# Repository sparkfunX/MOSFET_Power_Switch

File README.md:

SparkFun MOSFET Power Switch
========================================

[*SparkFun MOSFET Power Switch (COM-19799)*](https://www.sparkfun.com/products/19799)

Does your Arduino need to control a high voltage item, like a 12V LED strip, while needing to be powered as well? Do you want to avoid having multiple power adapters for your project and your Arduino? The MOSFET Power Switch is one of those products that we needed ourselves at SparkFun, so we figured other folks may have the same problem. Power the board with up to 12V and control up to 10A, all while providing sweet sweet 3.3V to your control board.

This board is ideal for turning on and off large loads such as solenoids, LEDs strips, and DC loads that may have back EMF. Simply pull the CTL pin low to activate the load. 3.3V, GND, and VCC are also provided at PTH headers. The load can be inserted into the poke-home connectors or soldered into PTH holes.

The MOSFET ([PSMN7R0-100BS](https://cdn.sparkfun.com/assets/6/9/3/8/1/PSMN7R0-100BS.pdf)) is rated to 100A/100V but we don't recommend you go much above 10A as the PCB traces become the limiter. The board 

Repository Contents
-------------------

* **/Hardware** - Eagle design files (.brd, .sch)

License Information
-------------------

This product is _**open source**_! 

Please review the LICENSE.md file for license information. 

If you have any questions or concerns on licensing, please contact technical support on our [SparkFun forums](https://forum.sparkfun.com/viewforum.php?f=152).

Distributed as-is; no warranty is given.

- Your friends at SparkFun.

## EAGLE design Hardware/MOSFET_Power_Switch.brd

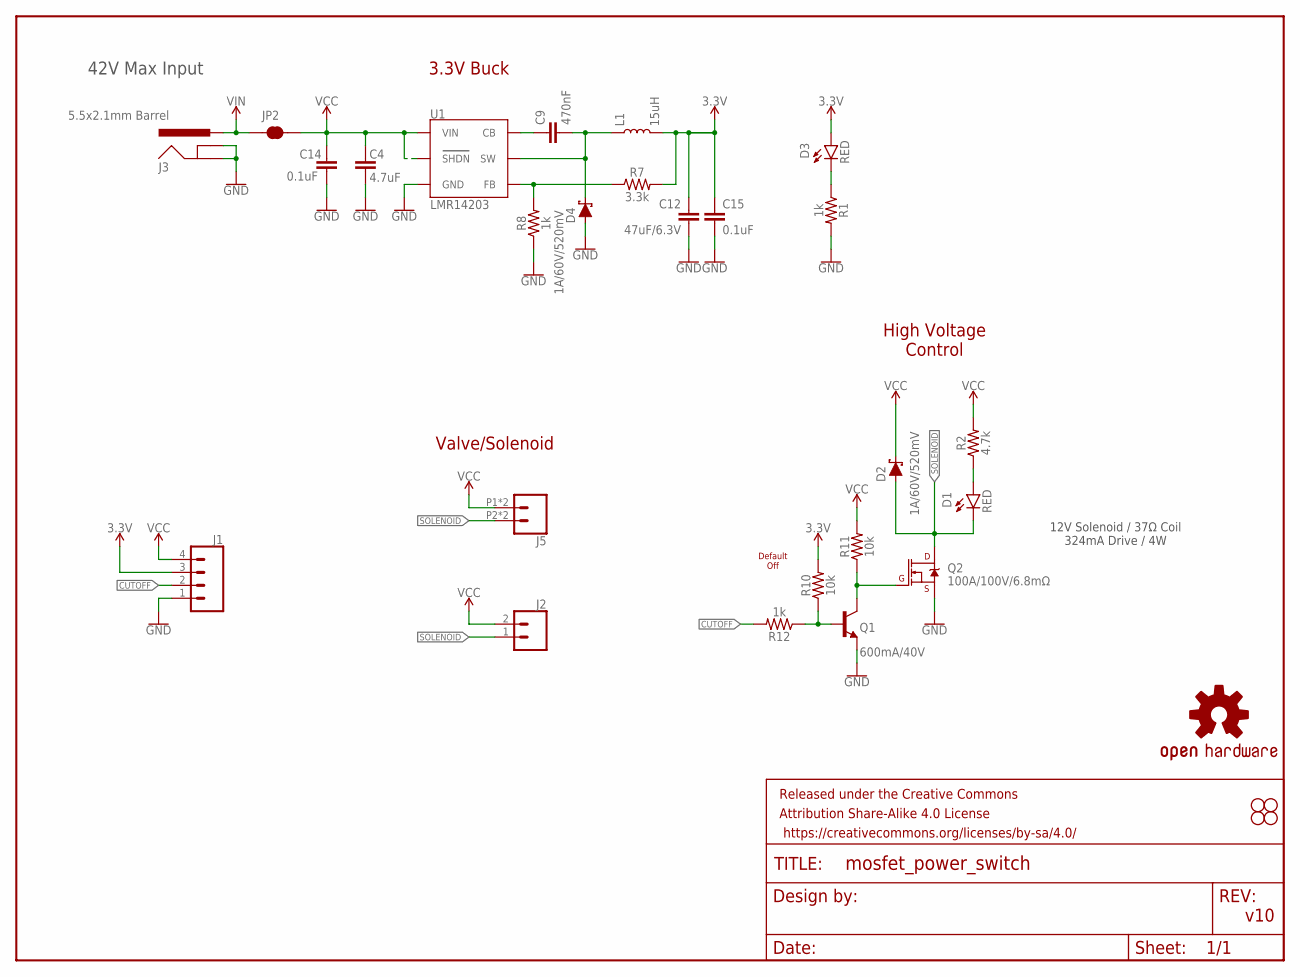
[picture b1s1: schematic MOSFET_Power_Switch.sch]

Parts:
C4: 4.7uF; 0603
C9: 470nF; 0603
C12: 47uF/6.3V; 0805
C14, C15: 0.1uF; 0603
D1, D3: RED; LED-0603
D2, D4: 1A/60V/520mV; DIODE-MICRO-SMP
FRAME2: FRAME-LETTER; CREATIVE_COMMONS
H1, H2, H3, H4: STAND-OFF
J1: CONN_041X04_NO_SILK_NO_POP; 1X04_NO_SILK
J2: CONN_021X02_NO_SILK; 1X02_NO_SILK
J3: 5.5x2.1mm Barrel; POWER_JACK_SMD
J5: CONN_02SMALL_POKEHOME; 1X02_POKEHOME
JP2: JUMPER-COMBO_2_NC_TRACE; COMBO-JUMPER_2_NC_TRACE
L1: 15uH; INDUCTOR_LQH32
LOGO1: OSHW-LOGOS; OSHW-LOGO-S
Q1: 600mA/40V; SOT23-3
Q2: 100A/100V/6.8mΩ; TO-263/D2PAK
R1, R8, R12: 1k; 0603
R2: 4.7k; 0603
R7: 3.3k; 0603
R10, R11: 10k; 0603
U1: LMR14203; SOT23-6

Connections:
3.3V: C12.1, C15.1, D3.A, J1.3, L1.P$2 (2), R7.2, R10.2
CUTOFF: J1.2, R12.2
GND: C4.2, C12.2, C14.2, C15.2, D4.A, J1.1, J3.GND (GNDBREAK), J3.P$4 (GND), Q1.2 (E), Q2.3 (S), R1.2, R8.1, U1.2 (GND)
unnamed: Q1.3 (C), Q2.1 (G), R11.1
unnamed: D1.A, R2.1
unnamed: D3.C, R1.1
unnamed: R7.1, R8.2, U1.3 (FB)
unnamed: C9.1, U1.1 (CB)
unnamed: Q1.1 (B), R10.1, R12.1
SOLENOID: D1.C, D2.A, J2.1, J5.P2 (2), J5.P4 (2), Q2.2 (D)
VCC: C4.1, C14.1, D2.C, J1.4, J2.2, J5.P1 (1), J5.P3 (1), JP2.2, JP2.4 (2), R2.2, R11.2, U1.4 (SHDN), U1.5 (VIN)
VIN: J3.VIN0 (PWR), JP2.1, JP2.3 (1)
VSW: C9.2, D4.C, L1.P$1 (1), U1.6 (SW)

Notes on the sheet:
v10
Default Off
Valve/Solenoid
High Voltage Control
3.3V Buck
12V Solenoid / 37Ω Coil 324mA Drive / 4W
42V Max Input

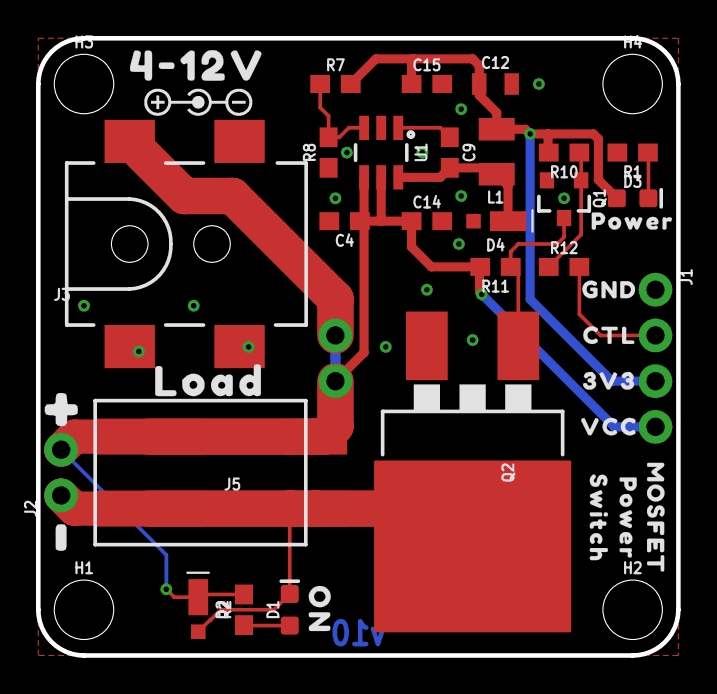
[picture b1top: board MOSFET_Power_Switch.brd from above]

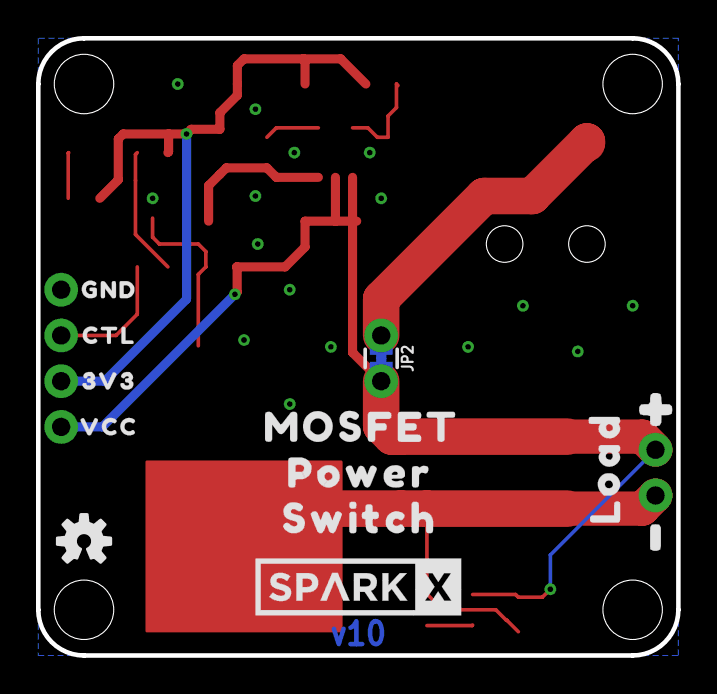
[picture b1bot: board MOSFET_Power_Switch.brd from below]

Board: 2 copper layers, 35.6 x 34.3 mm, 56 parts (13 on the bottom side), 13 nets.

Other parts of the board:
U$1, U$17: 3V32
U$2: MOSFET0
U$3, U$15: GND0
U$5, U$19: LOAD0
U$6: 4#12V0
U$7, U$18: VCC3
U$8, U$16: CTL0
U$9: POWER1
U$10, U$20: #0
U$11, U$22: #1
U$13: SWITCH2
U$21: SPARKX-LOGO5; SPARKX-LARGE
U$23: POWER0
U$24: MOSFET_0
U$25: POWER_1
U$26: SWITCH_2
U$29: POLARITY_MARKING_CENTER_POSITIVE#JPG
U$49: ON0

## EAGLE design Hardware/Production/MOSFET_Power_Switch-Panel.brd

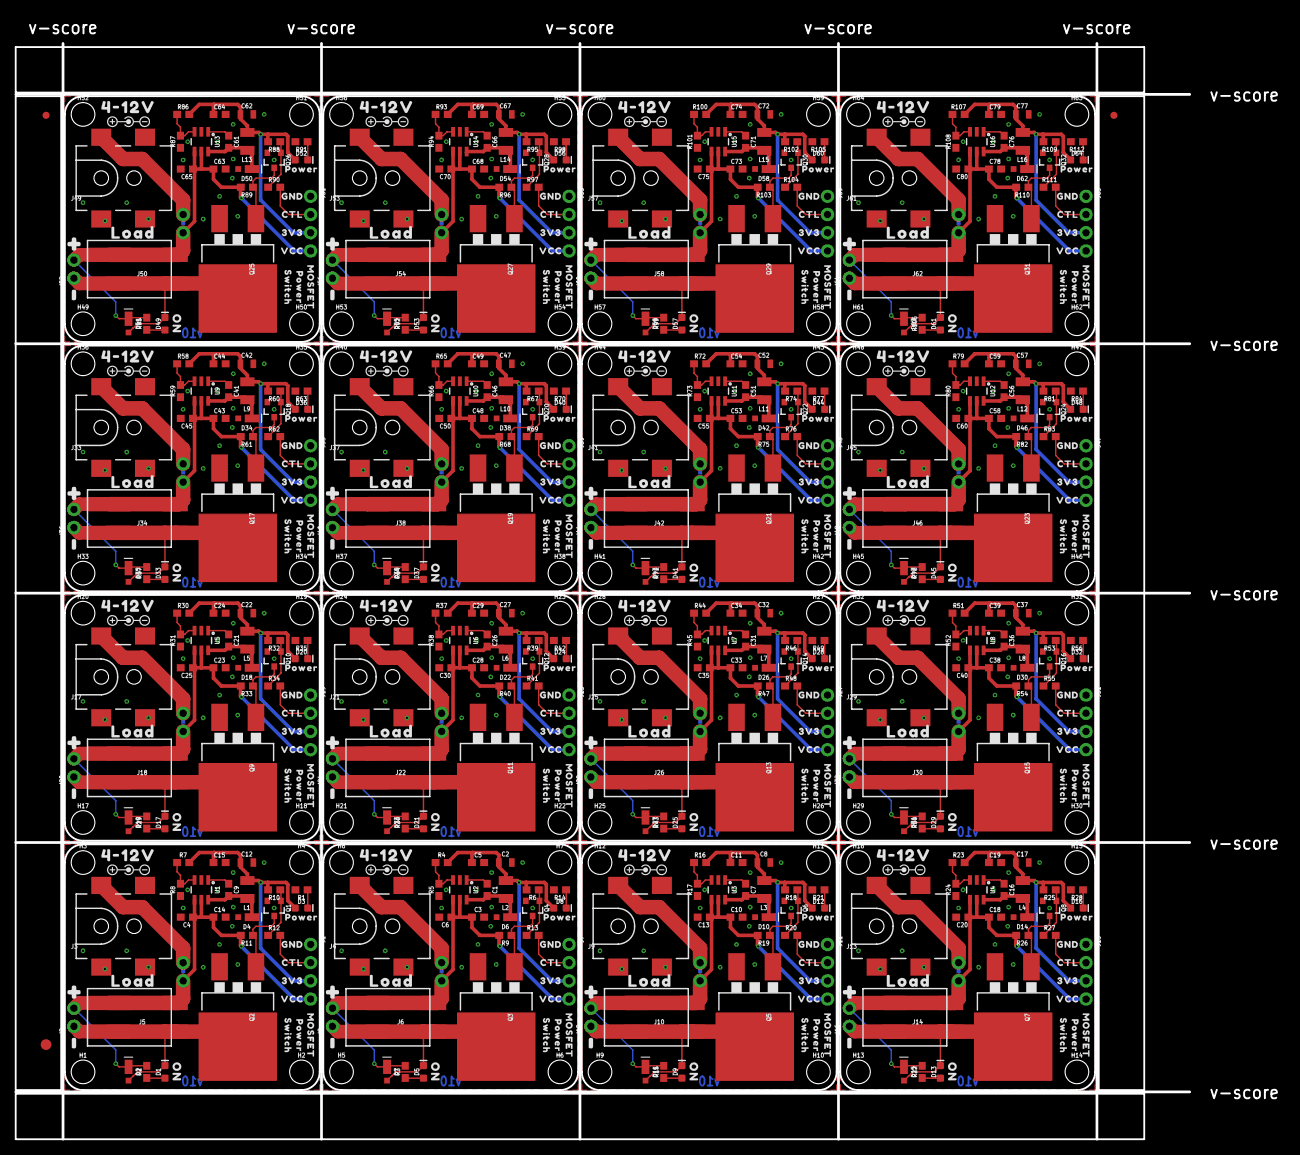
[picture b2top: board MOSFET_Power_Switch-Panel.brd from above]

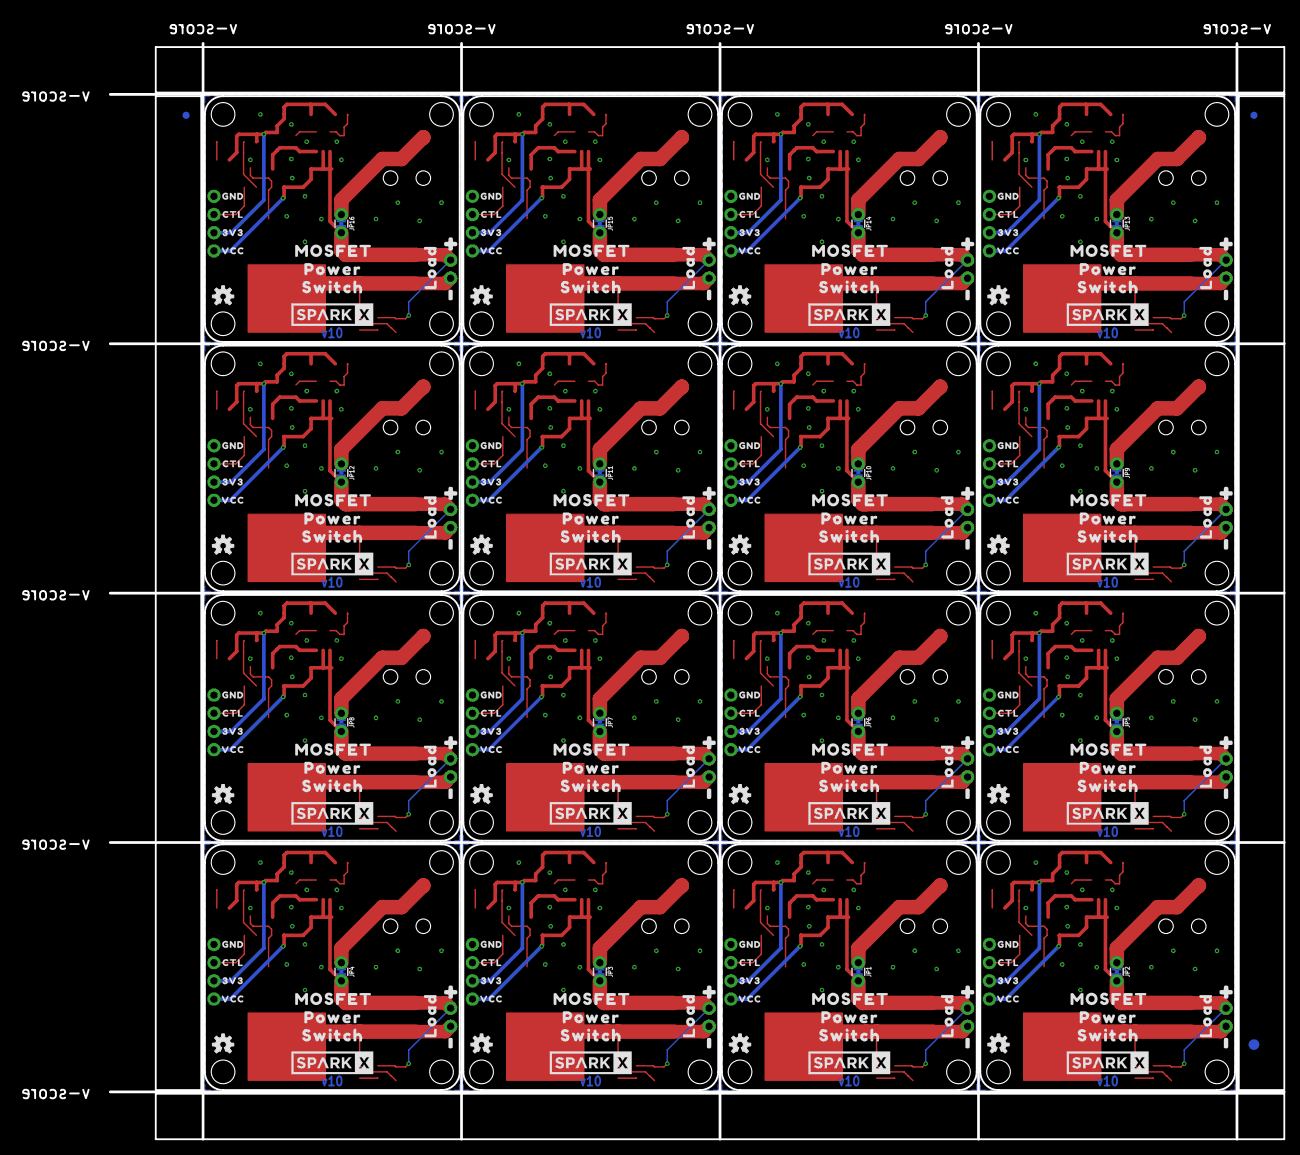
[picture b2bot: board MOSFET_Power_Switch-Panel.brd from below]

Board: 2 copper layers, 177.0 x 156.8 mm, 886 parts (211 on the bottom side), 208 nets.

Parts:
C1, C7, C9, C16, C21, C26, C31, C36, C41, C46, C51, C56, C61, C66, C71, C76: 470nF; 0603
C2, C8, C12, C17, C22, C27, C32, C37, C42, C47, C52, C57, C62, C67, C72, C77: 47uF/6.3V; 0805
C3, C5, C10, C11, C14, C15, C18, C19, C23, C24, C28, C29, C33, C34, C38, C39, C43, C44, C48, C49, C53, C54, C58, C59, C63, C64, C68, C69, C73, C74, C78, C79: 0.1uF; 0603
C4, C6, C13, C20, C25, C30, C35, C40, C45, C50, C55, C60, C65, C70, C75, C80: 4.7uF; 0603
D1, D3, D5, D8, D9, D12, D13, D16, D17, D20, D21, D24, D25, D28, D29, D32, D33, D36, D37, D40, D41, D44, D45, D48, D49, D52, D53, D56, D57, D60, D61, D64: RED; LED-0603
D2, D4, D6, D7, D10, D11, D14, D15, D18, D19, D22, D23, D26, D27, D30, D31, D34, D35, D38, D39, D42, D43, D46, D47, D50, D51, D54, D55, D58, D59, D62, D63: 1A/60V/520mV; DIODE-MICRO-SMP
E$1, E$2, E$3, E$4: FIDUCIAL-1X2
E$5, E$6: FIDUCIAL-1.5X3
H1, H2, H3, H4, H5, H6, H7, H8, H9, H10, H11, H12, H13, H14, H15, H16, H17, H18, H19, H20, H21, H22, H23, H24, H25, H26, H27, H28, H29, H30, H31, H32, H33, H34, H35, H36, H37, H38, H39, H40, H41, H42, H43, H44, H45, H46, H47, H48, H49, H50, H51, H52, H53, H54, H55, H56, H57, H58, H59, H60, H61, H62, H63, H64: STAND-OFF
J1, J7, J11, J15, J19, J23, J27, J31, J35, J39, J43, J47, J51, J55, J59, J63: 1X04_NO_SILK
J2, J8, J12, J16, J20, J24, J28, J32, J36, J40, J44, J48, J52, J56, J60, J64: 1X02_NO_SILK
J3, J4, J9, J13, J17, J21, J25, J29, J33, J37, J41, J45, J49, J53, J57, J61: 5.5x2.1mm Barrel; POWER_JACK_SMD
J5, J6, J10, J14, J18, J22, J26, J30, J34, J38, J42, J46, J50, J54, J58, J62: 1X02_POKEHOME
JP1, JP2, JP3, JP4, JP5, JP6, JP7, JP8, JP9, JP10, JP11, JP12, JP13, JP14, JP15, JP16: JUMPER-COMBO_2_NC_TRACE; COMBO-JUMPER_2_NC_TRACE
L1, L2, L3, L4, L5, L6, L7, L8, L9, L10, L11, L12, L13, L14, L15, L16: 15uH; INDUCTOR_LQH32
LOGO1, LOGO2, LOGO3, LOGO4, LOGO5, LOGO6, LOGO7, LOGO8, LOGO9, LOGO10, LOGO11, LOGO12, LOGO13, LOGO14, LOGO15, LOGO16: OSHW-LOGOS; OSHW-LOGO-S
Q1, Q4, Q6, Q8, Q10, Q12, Q14, Q16, Q18, Q20, Q22, Q24, Q26, Q28, Q30, Q32: 600mA/40V; SOT23-3
Q2, Q3, Q5, Q7, Q9, Q11, Q13, Q15, Q17, Q19, Q21, Q23, Q25, Q27, Q29, Q31: 100A/100V/6.8mΩ; TO-263/D2PAK
R1, R5, R8, R12, R13, R14, R17, R20, R21, R24, R27, R28, R31, R34, R35, R38, R41, R42, R45, R48, R49, R52, R55, R56, R59, R62, R63, R66, R69, R70, R73, R76, R77, R80, R83, R84, R87, R90, R91, R94, R97, R98, R101, R104, R105, R108, R111, R112: 1k; 0603
R2, R3, R15, R22, R29, R36, R43, R50, R57, R64, R71, R78, R85, R92, R99, R106: 4.7k; 0603
R4, R7, R16, R23, R30, R37, R44, R51, R58, R65, R72, R79, R86, R93, R100, R107: 3.3k; 0603
R6, R9, R10, R11, R18, R19, R25, R26, R32, R33, R39, R40, R46, R47, R53, R54, R60, R61, R67, R68, R74, R75, R81, R82, R88, R89, R95, R96, R102, R103, R109, R110: 10k; 0603
U1, U2, U3, U4, U5, U6, U7, U8, U9, U10, U11, U12, U13, U14, U15, U16: LMR14203; SOT23-6
U$1, U$17, U$31, U$38, U$57, U$64, U$82, U$89, U$107, U$114, U$132, U$139, U$157, U$164, U$182, U$189, U$207, U$214, U$232, U$239, U$257, U$264, U$282, U$289, U$307, U$314, U$332, U$339, U$357, U$364, U$382, U$389: 3V32
U$2, U$43, U$69, U$94, U$119, U$144, U$169, U$194, U$219, U$244, U$269, U$294, U$319, U$344, U$369, U$394: MOSFET0
U$3, U$15, U$32, U$36, U$58, U$62, U$83, U$87, U$108, U$112, U$133, U$137, U$158, U$162, U$183, U$187, U$208, U$212, U$233, U$237, U$258, U$262, U$283, U$287, U$308, U$312, U$333, U$337, U$358, U$362, U$383, U$387: GND0
U$4, U$21, U$51, U$76, U$101, U$126, U$151, U$176, U$201, U$226, U$251, U$276, U$301, U$326, U$351, U$376: SPARKX-LOGO5; SPARKX-LARGE
U$5, U$19, U$30, U$40, U$56, U$66, U$81, U$91, U$106, U$116, U$131, U$141, U$156, U$166, U$181, U$191, U$206, U$216, U$231, U$241, U$256, U$266, U$281, U$291, U$306, U$316, U$331, U$341, U$356, U$366, U$381, U$391: LOAD0
U$6, U$35, U$61, U$86, U$111, U$136, U$161, U$186, U$211, U$236, U$261, U$286, U$311, U$336, U$361, U$386: 4#12V0
U$7, U$18, U$33, U$39, U$59, U$65, U$84, U$90, U$109, U$115, U$134, U$140, U$159, U$165, U$184, U$190, U$209, U$215, U$234, U$240, U$259, U$265, U$284, U$290, U$309, U$315, U$334, U$340, U$359, U$365, U$384, U$390: VCC3
U$8, U$16, U$34, U$37, U$60, U$63, U$85, U$88, U$110, U$113, U$135, U$138, U$160, U$163, U$185, U$188, U$210, U$213, U$235, U$238, U$260, U$263, U$285, U$288, U$310, U$313, U$335, U$338, U$360, U$363, U$385, U$388: CTL0
U$9, U$44, U$70, U$95, U$120, U$145, U$170, U$195, U$220, U$245, U$270, U$295, U$320, U$345, U$370, U$395: POWER1
U$10, U$20, U$27, U$41, U$54, U$67, U$79, U$92, U$104, U$117, U$129, U$142, U$154, U$167, U$179, U$192, U$204, U$217, U$229, U$242, U$254, U$267, U$279, U$292, U$304, U$317, U$329, U$342, U$354, U$367, U$379, U$392: #0
U$11, U$22, U$28, U$42, U$55, U$68, U$80, U$93, U$105, U$118, U$130, U$143, U$155, U$168, U$180, U$193, U$205, U$218, U$230, U$243, U$255, U$268, U$280, U$293, U$305, U$318, U$330, U$343, U$355, U$368, U$380, U$393: #1
U$12, U$49, U$52, U$77, U$102, U$127, U$152, U$177, U$202, U$227, U$252, U$277, U$302, U$327, U$352, U$377: ON0
U$13, U$45, U$71, U$96, U$121, U$146, U$171, U$196, U$221, U$246, U$271, U$296, U$321, U$346, U$371, U$396: SWITCH2
U$14, U$29, U$53, U$78, U$103, U$128, U$153, U$178, U$203, U$228, U$253, U$278, U$303, U$328, U$353, U$378: POLARITY_MARKING_CENTER_POSITIVE#JPG
U$23, U$46, U$72, U$97, U$122, U$147, U$172, U$197, U$222, U$247, U$272, U$297, U$322, U$347, U$372, U$397: POWER0
U$24, U$47, U$73, U$98, U$123, U$148, U$173, U$198, U$223, U$248, U$273, U$298, U$323, U$348, U$373, U$398: MOSFET_0
U$25, U$48, U$74, U$99, U$124, U$149, U$174, U$199, U$224, U$249, U$274, U$299, U$324, U$349, U$374, U$399: POWER_1
U$26, U$50, U$75, U$100, U$125, U$150, U$175, U$200, U$225, U$250, U$275, U$300, U$325, U$350, U$375, U$400: SWITCH_2

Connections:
3.3V: C12.1, C15.1, D3.A, J1.3, L1.P$2, R7.2, R10.2
3.3V1: C2.1, C5.1, D8.A, J7.3, L2.P$2, R4.2, R6.2
3.3V2: C8.1, C11.1, D12.A, J11.3, L3.P$2, R16.2, R18.2
3.3V3: C17.1, C19.1, D16.A, J15.3, L4.P$2, R23.2, R25.2
3.3V4: C22.1, C24.1, D20.A, J19.3, L5.P$2, R30.2, R32.2
3.3V5: C27.1, C29.1, D24.A, J23.3, L6.P$2, R37.2, R39.2
3.3V6: C32.1, C34.1, D28.A, J27.3, L7.P$2, R44.2, R46.2
3.3V7: C37.1, C39.1, D32.A, J31.3, L8.P$2, R51.2, R53.2
3.3V8: C42.1, C44.1, D36.A, J35.3, L9.P$2, R58.2, R60.2
3.3V9: C47.1, C49.1, D40.A, J39.3, L10.P$2, R65.2, R67.2
3.3V10: C52.1, C54.1, D44.A, J43.3, L11.P$2, R72.2, R74.2
3.3V11: C57.1, C59.1, D48.A, J47.3, L12.P$2, R79.2, R81.2
3.3V12: C62.1, C64.1, D52.A, J51.3, L13.P$2, R86.2, R88.2
3.3V13: C67.1, C69.1, D56.A, J55.3, L14.P$2, R93.2, R95.2
3.3V14: C72.1, C74.1, D60.A, J59.3, L15.P$2, R100.2, R102.2
3.3V15: C77.1, C79.1, D64.A, J63.3, L16.P$2, R107.2, R109.2
CUTOFF: J1.2, R12.2
CUTOFF1: J7.2, R13.2
CUTOFF2: J11.2, R20.2
CUTOFF3: J15.2, R27.2
CUTOFF4: J19.2, R34.2
CUTOFF5: J23.2, R41.2
CUTOFF6: J27.2, R48.2
CUTOFF7: J31.2, R55.2
CUTOFF8: J35.2, R62.2
CUTOFF9: J39.2, R69.2
CUTOFF10: J43.2, R76.2
CUTOFF11: J47.2, R83.2
CUTOFF12: J51.2, R90.2
CUTOFF13: J55.2, R97.2
CUTOFF14: J59.2, R104.2
CUTOFF15: J63.2, R111.2
GND: C4.2, C12.2, C14.2, C15.2, D4.A, J1.1, J3.GND, J3.P$4, Q1.2, Q2.3, R1.2, R8.1, U1.2
GND1: C2.2, C3.2, C5.2, C6.2, D6.A, J4.GND, J4.P$4, J7.1, Q3.3, Q4.2, R5.1, R14.2, U2.2
GND2: C8.2, C10.2, C11.2, C13.2, D10.A, J9.GND, J9.P$4, J11.1, Q5.3, Q6.2, R17.1, R21.2, U3.2
GND3: C17.2, C18.2, C19.2, C20.2, D14.A, J13.GND, J13.P$4, J15.1, Q7.3, Q8.2, R24.1, R28.2, U4.2
GND4: C22.2, C23.2, C24.2, C25.2, D18.A, J17.GND, J17.P$4, J19.1, Q9.3, Q10.2, R31.1, R35.2, U5.2
GND5: C27.2, C28.2, C29.2, C30.2, D22.A, J21.GND, J21.P$4, J23.1, Q11.3, Q12.2, R38.1, R42.2, U6.2
GND6: C32.2, C33.2, C34.2, C35.2, D26.A, J25.GND, J25.P$4, J27.1, Q13.3, Q14.2, R45.1, R49.2, U7.2
GND7: C37.2, C38.2, C39.2, C40.2, D30.A, J29.GND, J29.P$4, J31.1, Q15.3, Q16.2, R52.1, R56.2, U8.2
GND8: C42.2, C43.2, C44.2, C45.2, D34.A, J33.GND, J33.P$4, J35.1, Q17.3, Q18.2, R59.1, R63.2, U9.2
GND9: C47.2, C48.2, C49.2, C50.2, D38.A, J37.GND, J37.P$4, J39.1, Q19.3, Q20.2, R66.1, R70.2, U10.2
GND10: C52.2, C53.2, C54.2, C55.2, D42.A, J41.GND, J41.P$4, J43.1, Q21.3, Q22.2, R73.1, R77.2, U11.2
GND11: C57.2, C58.2, C59.2, C60.2, D46.A, J45.GND, J45.P$4, J47.1, Q23.3, Q24.2, R80.1, R84.2, U12.2
GND12: C62.2, C63.2, C64.2, C65.2, D50.A, J49.GND, J49.P$4, J51.1, Q25.3, Q26.2, R87.1, R91.2, U13.2
GND13: C67.2, C68.2, C69.2, C70.2, D54.A, J53.GND, J53.P$4, J55.1, Q27.3, Q28.2, R94.1, R98.2, U14.2
GND14: C72.2, C73.2, C74.2, C75.2, D58.A, J57.GND, J57.P$4, J59.1, Q29.3, Q30.2, R101.1, R105.2, U15.2
GND15: C77.2, C78.2, C79.2, C80.2, D62.A, J61.GND, J61.P$4, J63.1, Q31.3, Q32.2, R108.1, R112.2, U16.2
unnamed: Q1.3, Q2.1, R11.1
unnamed: D1.A, R2.1
unnamed: D3.C, R1.1
unnamed: D5.A, R3.1
unnamed: R7.1, R8.2, U1.3
unnamed: R4.1, R5.2, U2.3
unnamed: C1.1, U2.1
unnamed: Q3.1, Q4.3, R9.1
unnamed: Q4.1, R6.1, R13.1
unnamed: C9.1, U1.1
unnamed: D8.C, R14.1
unnamed: Q1.1, R10.1, R12.1
unnamed: D9.A, R15.1
unnamed: R16.1, R17.2, U3.3
unnamed: C7.1, U3.1
unnamed: Q5.1, Q6.3, R19.1
unnamed: Q6.1, R18.1, R20.1
unnamed: D12.C, R21.1
unnamed: D13.A, R22.1
unnamed: R23.1, R24.2, U4.3
unnamed: C16.1, U4.1
unnamed: Q7.1, Q8.3, R26.1
unnamed: Q8.1, R25.1, R27.1
unnamed: D16.C, R28.1
unnamed: D17.A, R29.1
unnamed: R30.1, R31.2, U5.3
unnamed: C21.1, U5.1
unnamed: Q9.1, Q10.3, R33.1
unnamed: Q10.1, R32.1, R34.1
unnamed: D20.C, R35.1
unnamed: D21.A, R36.1
unnamed: R37.1, R38.2, U6.3
unnamed: C26.1, U6.1
unnamed: Q11.1, Q12.3, R40.1
unnamed: Q12.1, R39.1, R41.1
unnamed: D24.C, R42.1
unnamed: D25.A, R43.1
unnamed: R44.1, R45.2, U7.3
unnamed: C31.1, U7.1
unnamed: Q13.1, Q14.3, R47.1
unnamed: Q14.1, R46.1, R48.1
unnamed: D28.C, R49.1
unnamed: D29.A, R50.1
unnamed: R51.1, R52.2, U8.3
unnamed: C36.1, U8.1
unnamed: Q15.1, Q16.3, R54.1
unnamed: Q16.1, R53.1, R55.1
unnamed: D32.C, R56.1
unnamed: D33.A, R57.1
unnamed: R58.1, R59.2, U9.3
unnamed: C41.1, U9.1
unnamed: Q17.1, Q18.3, R61.1
unnamed: Q18.1, R60.1, R62.1
unnamed: D36.C, R63.1
unnamed: D37.A, R64.1
unnamed: R65.1, R66.2, U10.3
unnamed: C46.1, U10.1
unnamed: Q19.1, Q20.3, R68.1
unnamed: Q20.1, R67.1, R69.1
unnamed: D40.C, R70.1
unnamed: D41.A, R71.1
unnamed: R72.1, R73.2, U11.3
unnamed: C51.1, U11.1
unnamed: Q21.1, Q22.3, R75.1
unnamed: Q22.1, R74.1, R76.1
unnamed: D44.C, R77.1
unnamed: D45.A, R78.1
unnamed: R79.1, R80.2, U12.3
unnamed: C56.1, U12.1
unnamed: Q23.1, Q24.3, R82.1
unnamed: Q24.1, R81.1, R83.1
unnamed: D48.C, R84.1
unnamed: D49.A, R85.1
unnamed: R86.1, R87.2, U13.3
unnamed: C61.1, U13.1
unnamed: Q25.1, Q26.3, R89.1
unnamed: Q26.1, R88.1, R90.1
unnamed: D52.C, R91.1
unnamed: D53.A, R92.1
unnamed: R93.1, R94.2, U14.3
unnamed: C66.1, U14.1
unnamed: Q27.1, Q28.3, R96.1
unnamed: Q28.1, R95.1, R97.1
unnamed: D56.C, R98.1
unnamed: D57.A, R99.1
unnamed: R100.1, R101.2, U15.3
unnamed: C71.1, U15.1
unnamed: Q29.1, Q30.3, R103.1
unnamed: Q30.1, R102.1, R104.1
unnamed: D60.C, R105.1
unnamed: D61.A, R106.1
unnamed: R107.1, R108.2, U16.3
unnamed: C76.1, U16.1
unnamed: Q31.1, Q32.3, R110.1
unnamed: Q32.1, R109.1, R111.1
unnamed: D64.C, R112.1
SOLENOID: D1.C, D2.A, J2.1, J5.P2, J5.P4, Q2.2
SOLENOID1: D5.C, D7.A, J6.P2, J6.P4, J8.1, Q3.2
SOLENOID2: D9.C, D11.A, J10.P2, J10.P4, J12.1, Q5.2
SOLENOID3: D13.C, D15.A, J14.P2, J14.P4, J16.1, Q7.2
SOLENOID4: D17.C, D19.A, J18.P2, J18.P4, J20.1, Q9.2
SOLENOID5: D21.C, D23.A, J22.P2, J22.P4, J24.1, Q11.2
SOLENOID6: D25.C, D27.A, J26.P2, J26.P4, J28.1, Q13.2
SOLENOID7: D29.C, D31.A, J30.P2, J30.P4, J32.1, Q15.2
SOLENOID8: D33.C, D35.A, J34.P2, J34.P4, J36.1, Q17.2
SOLENOID9: D37.C, D39.A, J38.P2, J38.P4, J40.1, Q19.2
SOLENOID10: D41.C, D43.A, J42.P2, J42.P4, J44.1, Q21.2
SOLENOID11: D45.C, D47.A, J46.P2, J46.P4, J48.1, Q23.2
SOLENOID12: D49.C, D51.A, J50.P2, J50.P4, J52.1, Q25.2
SOLENOID13: D53.C, D55.A, J54.P2, J54.P4, J56.1, Q27.2
SOLENOID14: D57.C, D59.A, J58.P2, J58.P4, J60.1, Q29.2
SOLENOID15: D61.C, D63.A, J62.P2, J62.P4, J64.1, Q31.2
VCC: C4.1, C14.1, D2.C, J1.4, J2.2, J5.P1, J5.P3, JP2.2, JP2.4, R2.2, R11.2, U1.4, U1.5
VCC1: C3.1, C6.1, D7.C, J6.P1, J6.P3, J7.4, J8.2, JP1.2, JP1.4, R3.2, R9.2, U2.4, U2.5
VCC2: C10.1, C13.1, D11.C, J10.P1, J10.P3, J11.4, J12.2, JP3.2, JP3.4, R15.2, R19.2, U3.4, U3.5
VCC3: C18.1, C20.1, D15.C, J14.P1, J14.P3, J15.4, J16.2, JP4.2, JP4.4, R22.2, R26.2, U4.4, U4.5
VCC4: C23.1, C25.1, D19.C, J18.P1, J18.P3, J19.4, J20.2, JP5.2, JP5.4, R29.2, R33.2, U5.4, U5.5
VCC5: C28.1, C30.1, D23.C, J22.P1, J22.P3, J23.4, J24.2, JP6.2, JP6.4, R36.2, R40.2, U6.4, U6.5
VCC6: C33.1, C35.1, D27.C, J26.P1, J26.P3, J27.4, J28.2, JP7.2, JP7.4, R43.2, R47.2, U7.4, U7.5
VCC7: C38.1, C40.1, D31.C, J30.P1, J30.P3, J31.4, J32.2, JP8.2, JP8.4, R50.2, R54.2, U8.4, U8.5
VCC8: C43.1, C45.1, D35.C, J34.P1, J34.P3, J35.4, J36.2, JP9.2, JP9.4, R57.2, R61.2, U9.4, U9.5
VCC9: C48.1, C50.1, D39.C, J38.P1, J38.P3, J39.4, J40.2, JP10.2, JP10.4, R64.2, R68.2, U10.4, U10.5
VCC10: C53.1, C55.1, D43.C, J42.P1, J42.P3, J43.4, J44.2, JP11.2, JP11.4, R71.2, R75.2, U11.4, U11.5
VCC11: C58.1, C60.1, D47.C, J46.P1, J46.P3, J47.4, J48.2, JP12.2, JP12.4, R78.2, R82.2, U12.4, U12.5
VCC12: C63.1, C65.1, D51.C, J50.P1, J50.P3, J51.4, J52.2, JP13.2, JP13.4, R85.2, R89.2, U13.4, U13.5
VCC13: C68.1, C70.1, D55.C, J54.P1, J54.P3, J55.4, J56.2, JP14.2, JP14.4, R92.2, R96.2, U14.4, U14.5
VCC14: C73.1, C75.1, D59.C, J58.P1, J58.P3, J59.4, J60.2, JP15.2, JP15.4, R99.2, R103.2, U15.4, U15.5
VCC15: C78.1, C80.1, D63.C, J62.P1, J62.P3, J63.4, J64.2, JP16.2, JP16.4, R106.2, R110.2, U16.4, U16.5
VIN: J3.VIN0, JP2.1, JP2.3
VIN1: J4.VIN0, JP1.1, JP1.3
VIN2: J9.VIN0, JP3.1, JP3.3
VIN3: J13.VIN0, JP4.1, JP4.3
VIN4: J17.VIN0, JP5.1, JP5.3
VIN5: J21.VIN0, JP6.1, JP6.3
VIN6: J25.VIN0, JP7.1, JP7.3
VIN7: J29.VIN0, JP8.1, JP8.3
VIN8: J33.VIN0, JP9.1, JP9.3
VIN9: J37.VIN0, JP10.1, JP10.3
VIN10: J41.VIN0, JP11.1, JP11.3
VIN11: J45.VIN0, JP12.1, JP12.3
VIN12: J49.VIN0, JP13.1, JP13.3
VIN13: J53.VIN0, JP14.1, JP14.3
VIN14: J57.VIN0, JP15.1, JP15.3
VIN15: J61.VIN0, JP16.1, JP16.3
VSW: C9.2, D4.C, L1.P$1, U1.6
VSW1: C1.2, D6.C, L2.P$1, U2.6
VSW2: C7.2, D10.C, L3.P$1, U3.6
VSW3: C16.2, D14.C, L4.P$1, U4.6
VSW4: C21.2, D18.C, L5.P$1, U5.6
VSW5: C26.2, D22.C, L6.P$1, U6.6
VSW6: C31.2, D26.C, L7.P$1, U7.6
VSW7: C36.2, D30.C, L8.P$1, U8.6
VSW8: C41.2, D34.C, L9.P$1, U9.6
VSW9: C46.2, D38.C, L10.P$1, U10.6
VSW10: C51.2, D42.C, L11.P$1, U11.6
VSW11: C56.2, D46.C, L12.P$1, U12.6
VSW12: C61.2, D50.C, L13.P$1, U13.6
VSW13: C66.2, D54.C, L14.P$1, U14.6
VSW14: C71.2, D58.C, L15.P$1, U15.6
VSW15: C76.2, D62.C, L16.P$1, U16.6

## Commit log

2023-03-07 Update power jack

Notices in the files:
parts and their libraries:
SparkFun-Aesthetics: Licensing: Creative Commons ShareAlike 4.0 International - https://creativecommons.org/licenses/by-sa/4.0
SparkFun-Aesthetics: Released under the Creative Commons Attribution Share-Alike 4.0 License
SparkFun-Aesthetics: https://creativecommons.org/licenses/by-sa/4.0
